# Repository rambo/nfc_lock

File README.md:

nfc_lock
========

(more) secure electric lock with DESFire EV1 NFC tags

## libnfc and libfreefare

    sudo apt-add-repository ppa:christopher-hoskin/ppa
    sudo apt-get update
    sudo apt-get install libnfc5 libnfc-bin libnfc-pn53x-examples libnfc-examples
    sudo apt-get install libfreefare0 libfreefare-bin
    sudo apt-get install python-zmq python-yaml python-tornado

`python-yaml` and `python-tornado` can be installed to virtualenv (esp tornado might be better to install via pip even if not to virtualenv the deb pulls unneccessary dependencies), zmq will be painful to install via pip, use the system package.

### For compiling

For the C programs.

    sudo apt-get install libfreefare-dev libnfc-dev libssl-dev pkg-config libzmq-dev

### RasPi

All libraries should be part of normal releases now.

## Terms

  - Card (PICC in NXP terms): The DESFire EV1 chip+antenna in a package (fob, card, sticker...)
  - Pre-Personalization step: Where card default master key is changed and applications are defined.
  - Application: collection of files on the card, application can have multiple keys for various purposes
  - Provisioning (or personalization) step: Where a personalized card is issued to a card holder and the card (plus backing datababase) is updated with relevant info
  - Diversified key: Key that has been derived from a master key via the method described in NXP AN19022

## SQLite for keys

Create a test file `sqlite3 keys.db`:

    CREATE TABLE valid_tokens (value TEXT UNIQUE, type INTEGER, acl INTEGER, external_ids TEXT);
    CREATE TABLE revoked_tokens (value TEXT UNIQUE, type INTEGER);

Prepare some tags and insert their (real) UIDs to the grants and revokes

    INSERT INTO revoked_tokens VALUES ("04453069b21e80");
    INSERT INTO valid_tokens VALUES ("04212f69b21e80", 0, 1);

In reality you will generate this file based on your person registry (keep track of validity times etc there, then regenerate the keydb for the door).

## Hacking

Remember to valgrind your C programs (`valgrind -v --leak-check=yes  myprog args`) at the same time as you do general functionality testing.

### RasPi

It seems Valgrind does not (and will not) support some instructions we use to talk with the NFC chips, see (this stackoverflow)[valgrindworkaround] for a workaround.

[valgrindworkaround]: http://stackoverflow.com/questions/20066215/valgrind-unrecognizes-memcmp-instruction-in-raspberry-pi#comment-29892760

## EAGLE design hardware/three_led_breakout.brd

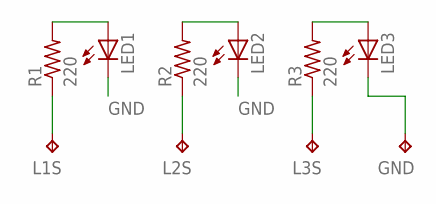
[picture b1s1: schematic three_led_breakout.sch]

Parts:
GND: TPTP13SQ; TP13SQ
L1S, L2S, L3S: TPTP13R; TP13R
LED1, LED2, LED3: LEDSML0603; SML0603
R1, R2, R3: 220; R0603

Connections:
GND: GND.TP, LED1.C, LED2.C, LED3.C
L1S: L1S.TP, R1.1
L2S: L2S.TP, R2.1
L3S: L3S.TP, R3.1
LEDSUPPLY: LED1.A, R1.2
LEDSUPPLY1: LED2.A, R2.2
LEDSUPPLY2: LED3.A, R3.2

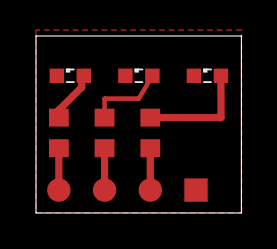
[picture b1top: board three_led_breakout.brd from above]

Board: 1 copper layer, 11.4 x 9.8 mm, 10 parts (0 on the bottom side), 7 nets.

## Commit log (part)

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2014-10-25 ignore OSX extra files
2014-10-25 some diagrams, originally drawn for http://skeemipesa.ee/tehnohack/en/
2014-10-25 debs built on raspbian wheezy (from jessie source packages)
2014-10-25 Go freefare package dependencies
2014-10-25 open the first libnfc configure device and print info
2014-10-25 remove the hello-world
2014-10-25 YAML parsing and hex-decoding test
2014-10-25 trying to figure out how to handle key diversification
2014-10-25 set the block limits correcty(?)
2014-10-25 add the 0x01 DIV constant
2014-10-25 implement using the test values from the AN
2014-10-25 fix key diversification for card sourced version
2014-10-25 simple poller
2014-10-25 run a heartbeat while polling for tags
2014-10-25 check the tag
2014-10-25 GPIO (untested)
2014-10-26 the constants are not up-to-date for B+
2014-10-26 cast correctly
2014-10-26 handle the relay too, refactor the teardown on interrupt
2014-10-26 rename the interrupt channel
2014-10-26 Added test program for desfire
2014-10-26 check ACL on raspi too
2014-10-26 use the default device
2014-10-26 sudo, hide the go install dir
2014-11-06 Started writing provisioning library by adding README.
2014-11-06 Added list of items to be commited.
2014-11-08 make a module out of this
2014-11-08 rename the function
2014-11-08 use the diversification library
2014-11-08 rethinking the applications and keys
2014-11-08 note about values being hex
2014-11-08 the GPIO config is node related and this way we still have 3 instead of 4 config files
2014-11-08 the canonical GPIO test cocode, LED blinker
2014-11-08 initially we just change the default key
2014-11-08 return nil as the value if there is an error
2014-11-09 UNTESTED: setting application keys
2014-11-09 some code to revert card back to clean state when we have fscked up
2014-11-09 tried to change order of key changes but still getting "unknown error", which most likely is actually authentication error (due to old libfreefare not setting errno correctly on authentication erorrs
2014-11-09 the first step is pre-personalization
2014-11-09 reminder to use backupfile for the ACL data too
2014-11-09 null AES key auth before changing application key 0 (aka provisioning key) worked, but getting problems when trying to change the other keys
2014-11-09 helper to calculate the settings flag (hopefully correctly)
2014-11-09 clean up old commented out code, update comments elsewhere
2014-11-09 make a module for the helpers (and rename them to start with capital letter so they are exported)
2014-11-09 make the YAML loading song&dance a helper
2014-11-09 read the ACL data back to uint64 so we can use boolean math to check for flags
2014-11-09 use the configured file ids here too, for some reason the second data file is not read fully...
2014-11-09 renamed the program
2014-11-09 for some reason the commit gives error, though AFAIUnderstand it must be done for backed up data files... changes are saved though
2014-11-09 fix tabs
2014-11-09 make it clear which data needs to be moved to personnel registry too
2014-11-09 found a bug while refactoring, the binary unpacking does not work as expected here
2014-11-09 started writing the actual relay controlling program, based on the test_gpio.go
2014-11-09 check for revoked keys
2014-11-09 explicit calld to disconnect since reconnecting to an already active tag will fail
2014-11-10 display the errors for connect too and retry
2014-11-11 try to optimize the memory use a bit, did not help with the weird malloc errors though
2014-11-11 heavy-handed refactoring
2014-11-11 remember to make those indices unique, also some notes about integer types
2014-11-11 it seems I was thinking of some other type casting issue
2014-11-11 refactored the card checking into a function
2014-11-11 fix logic error
2014-11-11 actually fix the logic error
2014-11-12 use different sqlite library
2014-11-12 also old code using old sqlite library and for prototyping anyway
2014-11-12 the channel version of course must be called as goroutine...
2014-11-12 senders close, receivers check for closed
2014-11-12 remove some (probably) unneccessary stuff
2014-11-14 trying to debug a segfault
2014-11-14 do not panic if gettags fauils
2014-11-14 disable GPIO since it fscks up gdb (due to epoll returning error instead of retrying on EINTR
2014-11-14 yes, getting desperate. memory is still corrupted somewhere
2014-11-14 skip profiling
2014-11-14 do this many times
2014-11-14 read in a loop to trigger memory error
2014-11-14 slightly more robust version, still crashes though
2014-11-14 do not slice
2014-11-15 check if passing the tag as pointer would cause a problem, not yet...
2014-11-15 just connecting and disconnecting does not seem to be enough to mess the heap
2014-11-15 this does not yet crash
2014-11-15 still no crash
2014-11-15 then again this does NOT crash
2014-11-15 switching to uint32 for ACL seems to work fine... go figure...
2014-11-15 after a couple of succesfull reads I now keep getting "unknown error" when re-authenticatingwith the ACL-read key (either key diversification gets fscked or something goes wrong in libfreefare
2014-11-15 this does not help with the "unknown error"
2014-11-15 it seems these two approaches return different result... anyway we lose the first byte at some poitn for reasons unknown...
2014-11-15 this seems reliable though
2014-11-15 let it run long enough and fatal error: markallocated: bad pointer
2014-11-15 be less noisy
2014-11-15 link to correct blog post
2014-11-15 ACL is now uint32 since with uint64 hings were crahsing left and right on x86 as well (where testing and debugging is easier)
2014-11-15 trying to compile these outside of libfreefare distribution
2014-11-15 I guess the first way is simpler
2014-11-15 test that the CMAC example compiles
2014-11-15 missed this one...
2014-11-15 add debugs
2014-11-15 need to pass the size correctly to the comparison function too
2014-11-15 make it possible to specify from cli how many times to run
2014-11-15 example headers for configuring keys etc
2014-11-15 opening the device works if I give the connstring from cli, the default "" does not...
2014-11-15 poll for tags, libfreefare seems to leak memory :(
    ==7894== HEAP SUMMARY:
    ==7894== in use at exit: 475 bytes in 41 blocks
    ==7894== total heap usage: 641 allocs, 600 frees, 64,749 bytes
    allocated
    ==7894==
    ==7894== Searching for pointers to 41 not-freed blocks
2014-11-15 ah, the other leak was my fault too...
    ==7932== HEAP SUMMARY:
    ==7932== in use at exit: 0 bytes in 0 blocks
    ==7932== total heap usage: 629 allocs, 629 frees, 61,243 bytes
    allocated
    ==7932==
    ==7932== All heap blocks were freed -- no leaks are possible
2014-11-15 mark the memory leak
2014-11-15 pass the tag to a handler function, so far so good
2014-11-15 print out what we actually parsed as the aid bytes
2014-11-15 selecting application works
2014-11-15 static key auth works
2014-11-16 pass the UID as string to key diversification because that is the way we get it from libfreefare
2014-11-16 prefix the helper too
2014-11-16 print the intermediate key bytes for debugging
2014-11-16 re-auth with ACL read key
2014-11-16 reading membership-id file
2014-11-16 tried to do something about the leak triggered by nfc_list_devices
2014-11-16 note about the timeout
2014-11-16 timeouts with pthreads but seems to leak
    ==10602== HEAP SUMMARY:
    ==10602== in use at exit: 1,632 bytes in 6 blocks
    ==10602== total heap usage: 736 allocs, 730 frees, 79,777 bytes
    allocated
    ==10602==
    ==10602== Searching for pointers to 6 not-freed blocks
2014-11-16 use phtread exit on the example too, but it too (possibly) leaks memory...
    do_or_timeout: calculation timed out
    --10711-- REDIR: 0x50d8870 (free) redirected to 0x4c2bd80 (free)
    ==10711==
    ==10711== HEAP SUMMARY:
    ==10711== in use at exit: 272 bytes in 1 blocks
    ==10711== total heap usage: 1 allocs, 0 frees, 272 bytes allocated
2014-11-16 cleaner way (also works when the infite loop is commented out)
2014-11-16 no leaks, yay!
2014-11-16 remove dead code, improve comments, add sanity-checks and defensive programming
2014-11-17 Added targets for different binaries.
2014-11-17 Fixed targets `all` and `clean`.
2014-11-17 Revert "Added list of items to be commited."
    This reverts commit 17f50deb2c7b290dcb1d74f95d18eb6c8d07dff4.
2014-11-17 Revert "Started writing provisioning library by adding README."
    This reverts commit 509e30bafb4f2d7743b81e3ccf9e4f74d4b1a0f4.
2014-11-24 loop and use correct receive method
2014-11-24 specify the uid on cli
2014-11-24 see if we can do event-based REQ/REP like this
2014-11-24 stub for serving key info over ZMQ
2014-11-24 still stub, config loading implemented
2014-11-24 the ioloop
2014-11-24 moar deps
2014-11-24 musings about logging the seen cards
2014-11-24 stub for accessing the python ZQM-REP server
2014-11-24 this juggling of libs flags did nothing
2014-11-24 remove the incorrect example code I copied for reference, this now works for receiving N part messages
2014-11-25 copy the read test as base for the actual gatekeeper
2014-11-25 add gatekeeper to Makefile
2014-11-25 fix comments
2014-11-25 output messages from ZMQ only in case of trouble
2014-11-28 better context name
2014-11-28 bind to pubsub socket, refactor string sending to a helper
2014-11-28 QnD test code for publish and subscribe
2014-11-28 all topics sub example
2014-11-28 use the result as topic, close the socket we failed to open before terminating the context or zmq hangs...
2014-12-01 trivial helper to handle gpio via sysfs
2014-12-01 copied configs for the old watcher, QnD ZMQ "port" (does not yet actually act upon cards)
2014-12-01 bypass couchdb errors when logging
2014-12-01 add FAKE mode for testing on VMs etc
2014-12-01 handle the results coming over ZMQ
2014-12-03 small breakout for three status leds
2014-12-04 on raspbian we must specify -lrt
2014-12-04 note about a problem when perosnalizing
2014-12-08 QnD upstart scripts based on old ones from elsewhere
2014-12-08 script to make a tarball you can uncompress on your target node so it does not have to contain the build dependencies
2014-12-08 leave the directory before removing it
2014-12-08 be quiet
2014-12-09 start pre-personalization code based on the read_personalized code
2014-12-09 make a separate program for formatting the card (de-personalize)
2014-12-09 keep the nullkey as global
2014-12-09 print the errors
2014-12-09 this seems to make no difference either way
2014-12-09 still getting LENGTH_ERROR when trying to change the Application master key
2014-12-09 at least I get different error but I cannot figure out when I should use the set_default_key and when change_key
2014-12-09 this function specifies the crypto anyway
2014-12-10 the "member-id" (to be renamed) file will contain a pseudorandom uint32 that is unique and persistent for a person in our system
2014-12-10 convert to use the helpers
2014-12-10 QnD personalization tool still needs work
2014-12-11 reading the value from the card works fine but for some reason the stack protector does not like us when we try to assign the value
2014-12-11 no need to init these
2014-12-11 do not leak memory
2014-12-11 enable random-id, do not leak
2014-12-11 updated the table telling where various keys are needed
2014-12-11 updated the concept, we have only one application
2014-12-14 sleep less if the personalization failed
2014-12-14 explicitly enable the stack protector
2014-12-14 note about valgrind on raspi
2015-01-15 logging helpers
2015-01-15 added important reminder
2015-02-18 it seems that for UPiS NO is the new NC, and we have to use external relay...
2015-03-24 list log.c only once
2015-03-24 use the log helpers for messages
2015-03-24 ignore the log_test binary
2017-03-18 Ignore IDE files
2017-03-18 Update README for new format db
2020-05-20 Updated ZMQ calls to current version
2020-05-24 Updated zqm calls
2020-05-24 Python3 string/bytes update
2020-05-24 Added heartbeat and installation items
2020-05-28 Fixed key db origin path
2020-05-28 Moved ZMQ to localhost instead of 0.0.0.0
2020-07-29 Added missing systemd service files
